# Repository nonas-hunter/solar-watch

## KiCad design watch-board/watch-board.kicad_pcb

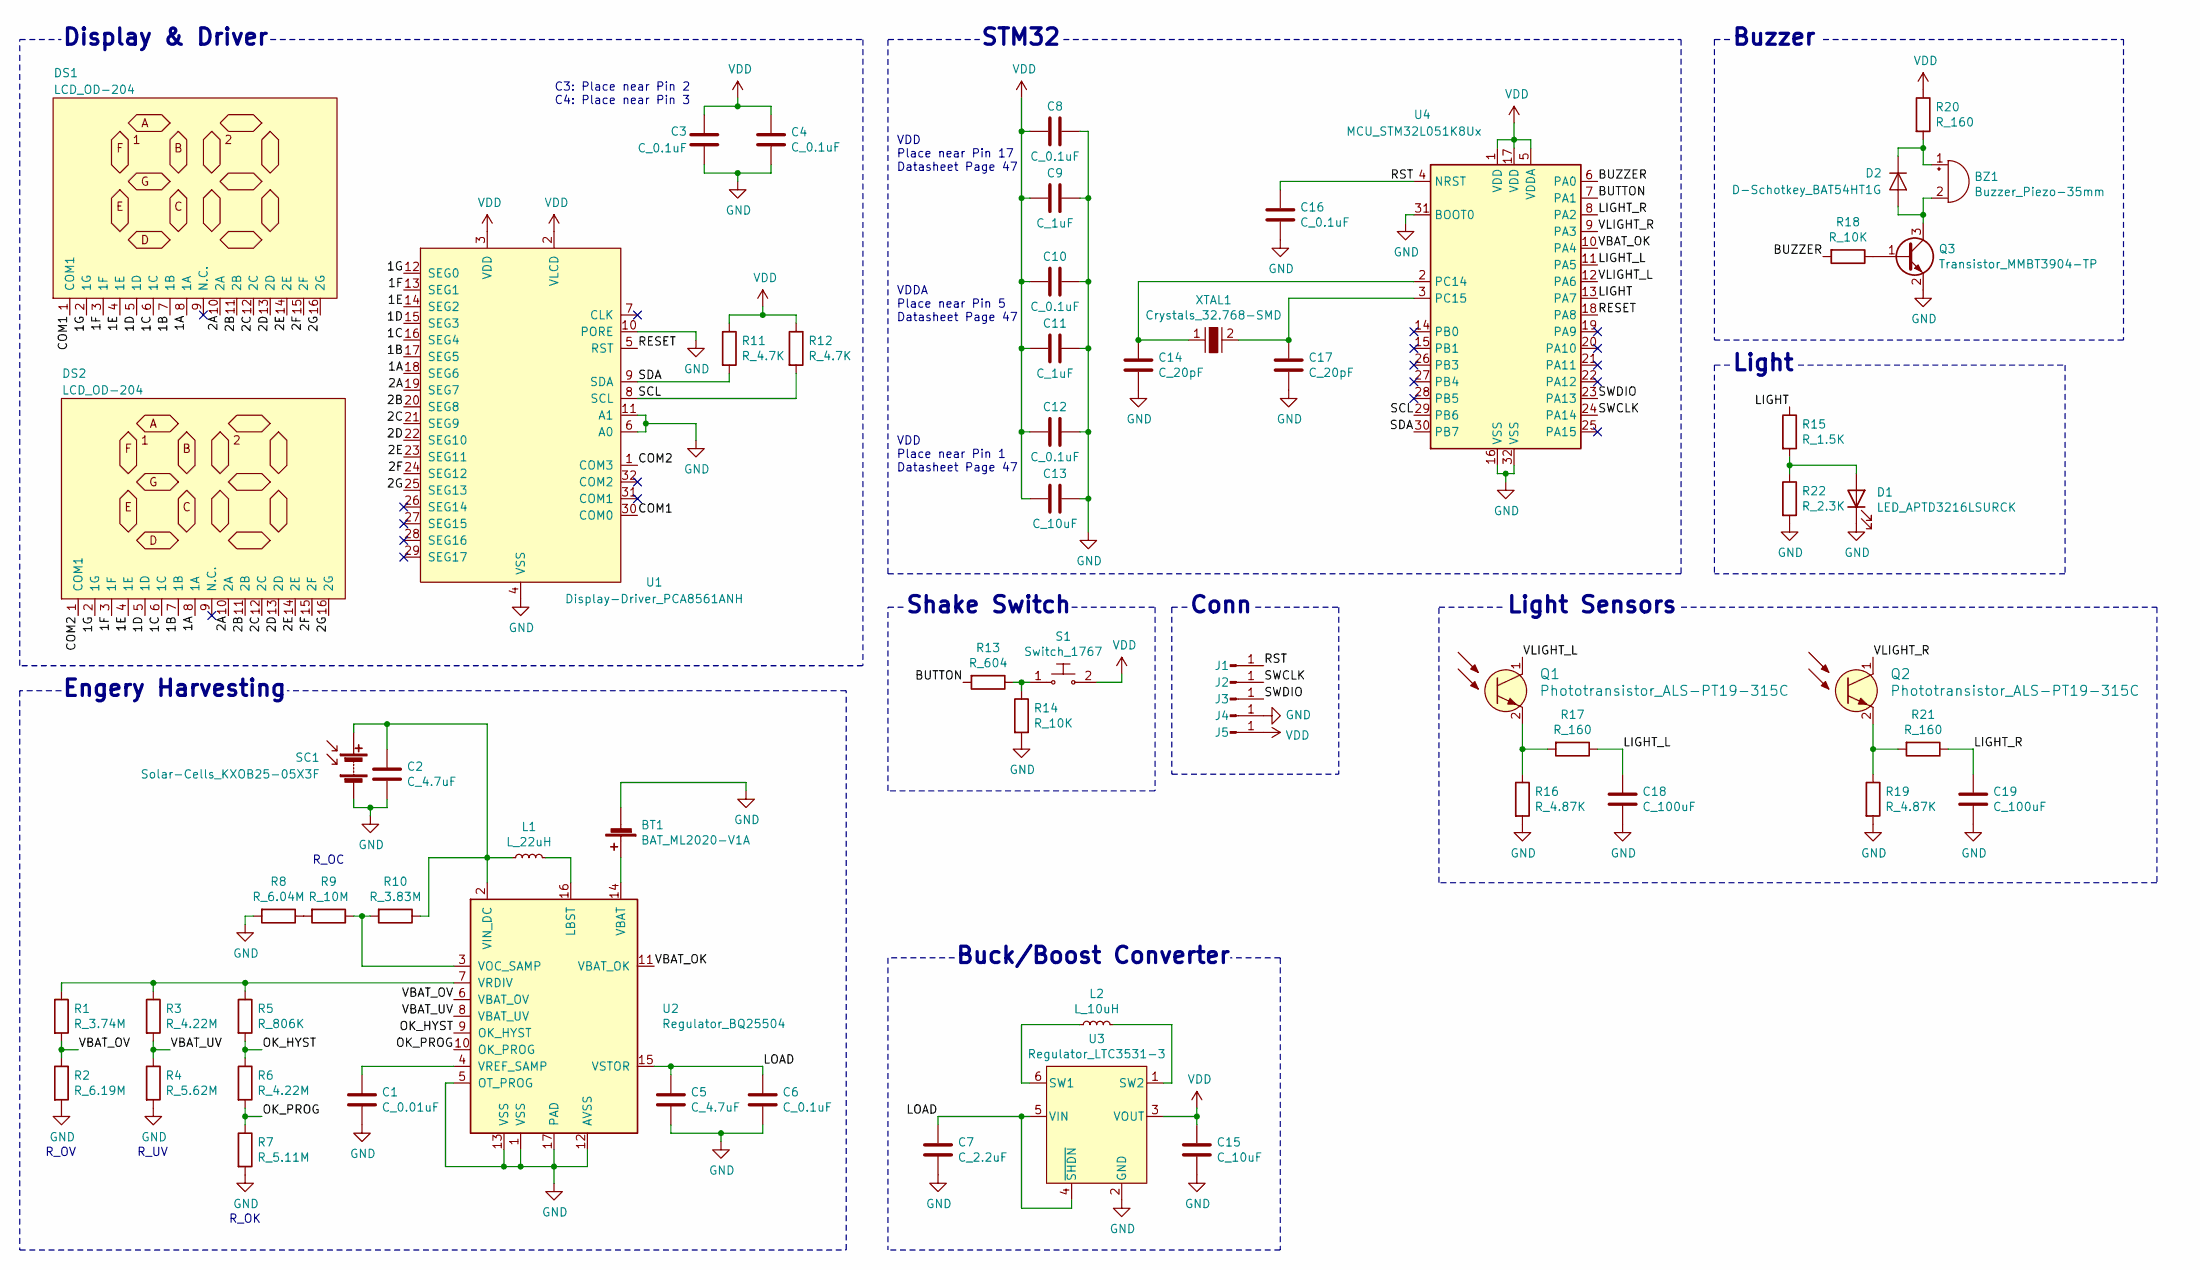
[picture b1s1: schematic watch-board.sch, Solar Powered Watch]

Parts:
BT1: BAT_ML2020-V1A; Battery_Panasonic-ML-2020-V1A; Digi-Key_PN P045-ND
BZ1: Buzzer_Piezo-35mm; Fuse_Littelfuse-NANO2-451_453
C1: C_0.01uF; C_0805_2012Metric; Digi-Key_PN 399-17617-1-ND
C2, C5: C_4.7uF; C_0805_2012Metric; Digi-Key_PN 399-7415-1-ND
C3, C4, C6, C8, C10, C12, C16: C_0.1uF; C_0805_2012Metric; Digi-Key_PN 399-8000-1-ND
C7: C_2.2uF; C_0805_2012Metric; Digi-Key_PN 311-3438-1-ND
C9, C11: C_1uF; C_0805_2012Metric; Digi-Key_PN 311-1909-1-ND
C13, C15: C_10uF; C_0805_2012Metric; Digi-Key_PN 399-4925-1-ND
C14, C17: C_20pF; C_0805_2012Metric; Digi-Key_PN 311-4221-1-ND
C18, C19: C_100uF; C_0805_2012Metric; Digi-Key_PN 490-13981-2-ND
D1: LED_APTD3216LSURCK; LED_1206_3216Metric; Digi-Key_PN 754-2050-6-ND
D2: D-Schotkey_BAT54HT1G; D_SOD-323; Digi-Key_PN BAT54HT1GOSCT-ND
DS1, DS2: LCD_OD-204; Digi-Key_PN 2544-OD-204-ND
J1, J2, J3, J4, J5: Conn_PAD; Connector_PAD_1mm_Circ
L1: L_22uH; L_Wuerth_WE-TPC-3816; Digi-Key_PN 732-1012-1-ND
L2: L_10uH; L_1812_4532Metric; Digi-Key_PN 490-2519-1-ND
Q1, Q2: Phototransistor_ALS-PT19-315C; LED_2-SMD_No_Lead_1.7x0.8mm; MPN ALS-PT19-315C/L177/TR8; Digi-Key_PN 1080-1244-1-ND
Q3: Transistor_MMBT3904-TP; SOT-23; Digi-Key_PN MMBT3904TPMSCT-ND
R1: R_3.74M; R_0805_2012Metric; Digi-Key_PN 541-3.74MCCT-ND
R2: R_6.19M; R_0805_2012Metric; Digi-Key_PN 311-6.19MCRCT-ND
R3, R6: R_4.22M; R_0805_2012Metric; Digi-Key_PN 2019-RK73H2ATTD4224FCT-ND
R4: R_5.62M; R_0805_2012Metric; Digi-Key_PN 311-5.62MCRCT-ND
R5: R_806K; R_0805_2012Metric; Digi-Key_PN 311-806KCRCT-ND
R7: R_5.11M; R_0805_2012Metric; Digi-Key_PN 311-5.11MCRCT-ND
R8: R_6.04M; R_0805_2012Metric; Digi-Key_PN 311-6.04MCRCT-ND
R9: R_10M; R_0805_2012Metric; Digi-Key_PN 311-10MARDKR-ND
R10: R_3.83M; R_0805_2012Metric; Digi-Key_PN 541-3.83MCCT-ND
R11, R12: R_4.7K; R_0805_2012Metric; Digi-Key_PN 311-4.70KCRCT-ND
R13: R_604; R_0805_2012Metric; Digi-Key_PN P604DACT-ND
R14, R18: R_10K; R_0805_2012Metric; Digi-Key_PN 311-10.0KCRCT-ND
R15: R_1.5K; R_0805_2012Metric; Digi-Key_PN A129751CT-ND
R16, R19: R_4.87K; R_0805_2012Metric; Digi-Key_PN 2019-RK73H2ATTD4871FCT-ND
R17, R20, R21: R_160; R_0805_2012Metric; Digi-Key_PN 311-160ARCT-ND
R22: R_2.3K; R_0805_2012Metric; Digi-Key_PN RNCP0805FTD2K32CT-ND
S1: Switch_1767; PinSocket_1x02_P2.54mm_Vertical; Digi-Key_PN 1528-2159-ND
SC1: Solar-Cells_KXOB25-05X3F; Solar-Cells_KXOB25; Digi-Key_PN KXOB25-05X3FCT-ND
U1: Display-Driver_PCA8561ANH; QFN-32-1EP_5x5mm_P0.5mm_EP3.6x3.6mm; Digi-Key_PN 568-13032-1-ND
U2: Regulator_BQ25504; VQFN-16-1EP_3x3mm_P0.5mm_EP1.8x1.8mm_ThermalVias; Digi-Key_PN 296-29741-1-ND
U3: Regulator_LTC3531-3; TSOT-23-6; Digi-Key_PN LTC3531ES6-3#TRMPBFCT-ND
U4: MCU_STM32L051K8Ux; QFN-32-1EP_5x5mm_P0.5mm_EP3.3x3.3mm; Digi-Key_PN 497-17490-ND
XTAL1: Crystals_32.768-SMD; SMD-2_3.2x1.5mm; MPN ECS-.327-12.5-34B-TR; Digi-Key_PN XC1617CT-ND

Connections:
/1A: DS1.8 (1A), DS2.8 (1A), U1.18 (SEG6)
/1B: DS1.7 (1B), DS2.7 (1B), U1.17 (SEG5)
/1C: DS1.6 (1C), DS2.6 (1C), U1.16 (SEG4)
/1D: DS1.5 (1D), DS2.5 (1D), U1.15 (SEG3)
/1E: DS1.4 (1E), DS2.4 (1E), U1.14 (SEG2)
/1F: DS1.3 (1F), DS2.3 (1F), U1.13 (SEG1)
/1G: DS1.2 (1G), DS2.2 (1G), U1.12 (SEG0)
/2A: DS1.10 (2A), DS2.10 (2A), U1.19 (SEG7)
/2B: DS1.11 (2B), DS2.11 (2B), U1.20 (SEG8)
/2C: DS1.12 (2C), DS2.12 (2C), U1.21 (SEG9)
/2D: DS1.13 (2D), DS2.13 (2D), U1.22 (SEG10)
/2E: DS1.14 (2E), DS2.14 (2E), U1.23 (SEG11)
/2F: DS1.15 (2F), DS2.15 (2F), U1.24 (SEG12)
/2G: DS1.16 (2G), DS2.16 (2G), U1.25 (SEG13)
/BUTTON: R13.2, U4.7 (PA1)
/BUZZER: R18.2, U4.6 (PA0)
/COM1: DS1.1 (COM1), U1.30 (COM0), U1.32 (COM2)
/COM2: DS2.1 (COM1), U1.1 (COM3), U1.31 (COM1)
/LIGHT: R15.1, U4.13 (PA7)
/LIGHT_L: C18.1, R17.1, U4.11 (PA5)
/LIGHT_R: C19.1, R21.1, U4.8 (PA2)
/LOAD: C5.1, C6.1, C7.1, U2.15 (VSTOR), U3.4 (~SHDN), U3.5 (VIN)
/OK_HYST: R5.2, R6.1, U2.9 (OK_HYST)
/OK_PROG: R6.2, R7.1, U2.10 (OK_PROG)
/RESET: U1.5 (RST), U4.18 (PA8)
/RST: C16.1, J1.1, U4.4 (NRST)
/SCL: R12.2, U1.8 (SCL), U4.29 (PB6)
/SDA: R11.2, U1.9 (SDA), U4.30 (PB7)
/SWCLK: J2.1, U4.24 (PA14)
/SWDIO: J3.1, U4.23 (PA13)
/VBAT_OK: U2.11 (VBAT_OK), U4.10 (PA4)
/VBAT_OV: R1.2, R2.1, U2.6 (VBAT_OV)
/VBAT_UV: R3.2, R4.1, U2.8 (VBAT_UV)
/VLIGHT_L: Q1.1 (C), U4.12 (PA6)
/VLIGHT_R: Q2.1 (C), U4.9 (PA3)
GND: BT1.Neg (-), C1.2, C2.2, C3.2, C4.2, C5.2, C6.2, C7.2, C8.1, C9.1, C10.1, C11.1, C12.1, C13.1, C14.2, C15.2, C16.2, C17.2, C18.2, C19.2, D1.1 (K), J4.1, Q3.2 (E), R2.2, R4.2, R7.2, R8.2, R14.2, R16.2, R19.2, R22.2, SC1.2 (-), U1.4 (VSS), U1.6 (A0), U1.10 (PORE), U1.11 (A1), U2.1 (VSS), U2.5 (OT_PROG), U2.12 (AVSS), U2.13 (VSS), U2.17 (PAD), U3.2 (GND), U4.16 (VSS), U4.31 (BOOT0), U4.32 (VSS)
unnamed: BT1.Pos (+), U2.14 (VBAT)
unnamed: BZ1.1 (-), D2.1 (K), R20.2
unnamed: BZ1.2 (+), D2.2 (A), Q3.3 (C)
unnamed: C1.1, U2.4 (VREF_SAMP)
unnamed: C2.1, L1.1, R10.1, SC1.1 (+), U2.2 (VIN_DC)
unnamed: C14.1, U4.2 (PC14), XTAL1.1
unnamed: C17.1, U4.3 (PC15), XTAL1.2
unnamed: D1.2 (A), R15.2, R22.1
unnamed: L1.2, U2.16 (LBST)
unnamed: L2.1, U3.6 (SW1)
unnamed: L2.2, U3.1 (SW2)
unnamed: Q1.2 (E), R16.1, R17.2
unnamed: Q2.2 (E), R19.1, R21.2
unnamed: Q3.1 (B), R18.1
unnamed: R1.1, R3.1, R5.1, U2.7 (VRDIV)
unnamed: R8.1, R9.2
unnamed: R9.1, R10.2, U2.3 (VOC_SAMP)
unnamed: R13.1, R14.1, S1.1
VDD: C3.1, C4.1, C8.2, C9.2, C10.2, C11.2, C12.2, C13.2, C15.1, J5.1, R11.1, R12.1, R20.1, S1.2, U1.2 (VLCD), U1.3 (VDD), U3.3 (VOUT), U4.1 (VDD), U4.5 (VDDA), U4.17 (VDD)

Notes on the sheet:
VDDA Place near Pin 5 Datasheet Page 47
VDD Place near Pin 17 Datasheet Page 47
VDD Place near Pin 1 Datasheet Page 47
STM32
Buck/Boost Converter
Shake Switch
Conn
Engery Harvesting
R_UV
R_OV
R_OK
R_OC
Display & Driver
Buzzer
Light
Light Sensors
C3: Place near Pin 2 C4: Place near Pin 3

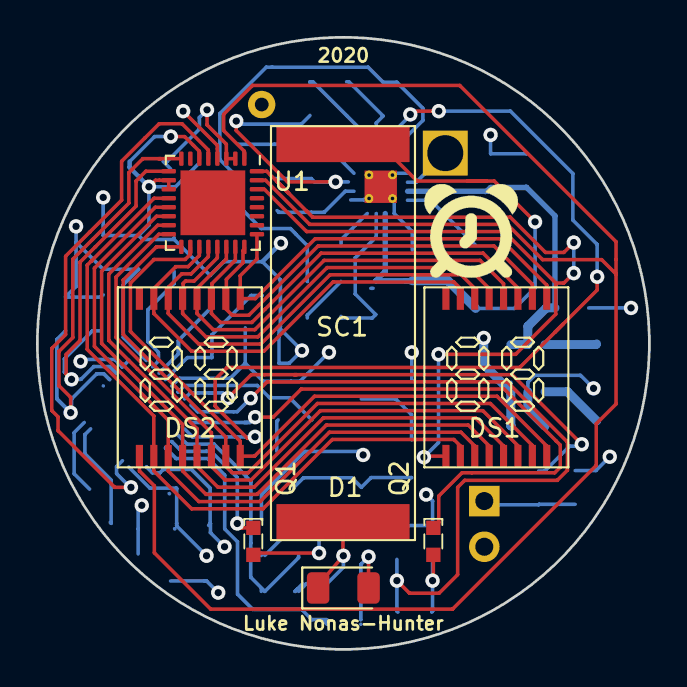
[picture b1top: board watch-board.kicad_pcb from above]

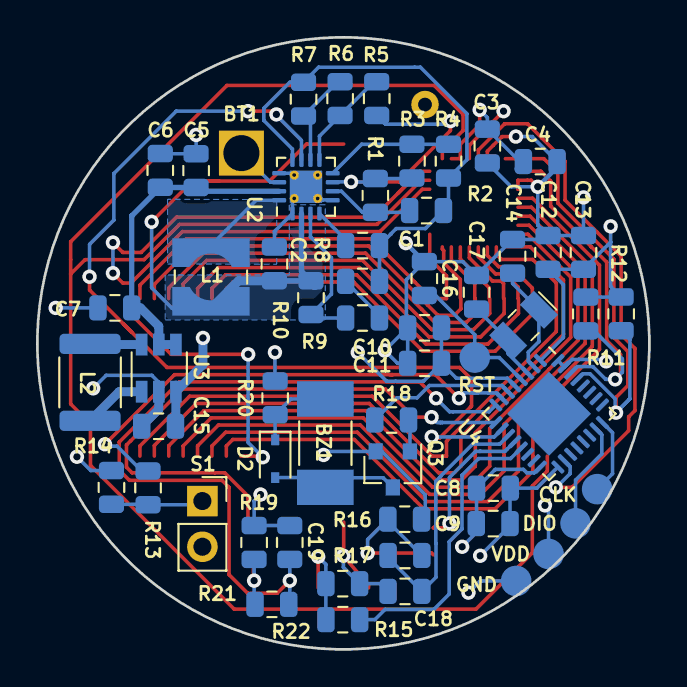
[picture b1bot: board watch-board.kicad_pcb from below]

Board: 4 copper layers, 34.0 x 34.0 mm, 64 parts (57 on the bottom side), 55 nets.

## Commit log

2020-04-23 creating repository -- adding gitignore
2020-04-23 making KiCad files
2020-04-23 adding components
2020-04-24 setting up linear voltage regulator at 3.1V
2020-04-24 adding battery and solar cell
2020-05-10 power management desgin complete
2020-05-12 adding bypass caps to STM32
2020-05-13 adding TODOs
2020-05-13 adding more TODOs
2020-05-14 switching to LTC3105 for power harvesting
2020-05-15 switching to BQ25570 & LTC3531 combo
2020-05-15 finished LTC3531-3 design
2020-06-21 finished REV1 of board
2020-06-26 starting design of multi level watch
2020-07-08 Schematic for Version 2
2020-07-08 required files for watch-V2
2020-08-17 Stopping work on Watch-V2. Changing driver & Display on Watch-V1.
2020-08-18 Adding Phototransistors for Gesture Sensing
2020-08-19 design complete TODO: add justifications for component choice
2020-08-19 adding current limiting resistor to buzzer
2020-08-19 removing multilayered watch design
2020-08-19 starting circuit justification documentation
2020-08-19 Confirming shake-switch circuit -- adjusting pull-down and current limiting resistor
2020-08-20 Added light sensor justification to documentation
2020-08-20 creating documentation folder, adding BQ25504 spread sheet, finalizing justication doc
2020-08-20 Rearranging Schematic
2020-08-27 Starting Layout -- updated parts with smaller footprints for better layout
2020-08-27 Layout (Rev 1) Complete
2020-08-28 starting layout. connected LCDs
2020-08-28 final LCD placement
2020-08-29 wiring layout for LCDs v2
2020-08-29 LCDs placed for best wiring
2020-08-30 LCDs fully wired :)
2020-09-01 all wiring done except gnd
2020-09-02 finished wiring
2020-09-03 creating 4 layer alt
2020-09-03 four layer complete -- need to do silk screen
2020-09-03 updating documentation on LED
2020-09-03 removing four-layer board
2020-09-03 removing two-layer board -- moved to new branch
2020-09-03 renaming 4-layer project for ease of use
2020-09-03 downloaded possible silk screen graphic
2020-09-03 added silk screen
2020-09-03 connecting chain to ground
2020-09-03 rebuilding power layers
2021-01-07 Change folder names
2021-01-07 Change folder name
2021-01-08 Change documentation folder name
2021-01-08 Change watch board folder name
2021-01-09 Add consumer interview notes
2021-01-09 Write basic watch description
2021-03-03 Add footprint diagram to documentation
2021-03-03 Design schematic with basic watch functionalities
